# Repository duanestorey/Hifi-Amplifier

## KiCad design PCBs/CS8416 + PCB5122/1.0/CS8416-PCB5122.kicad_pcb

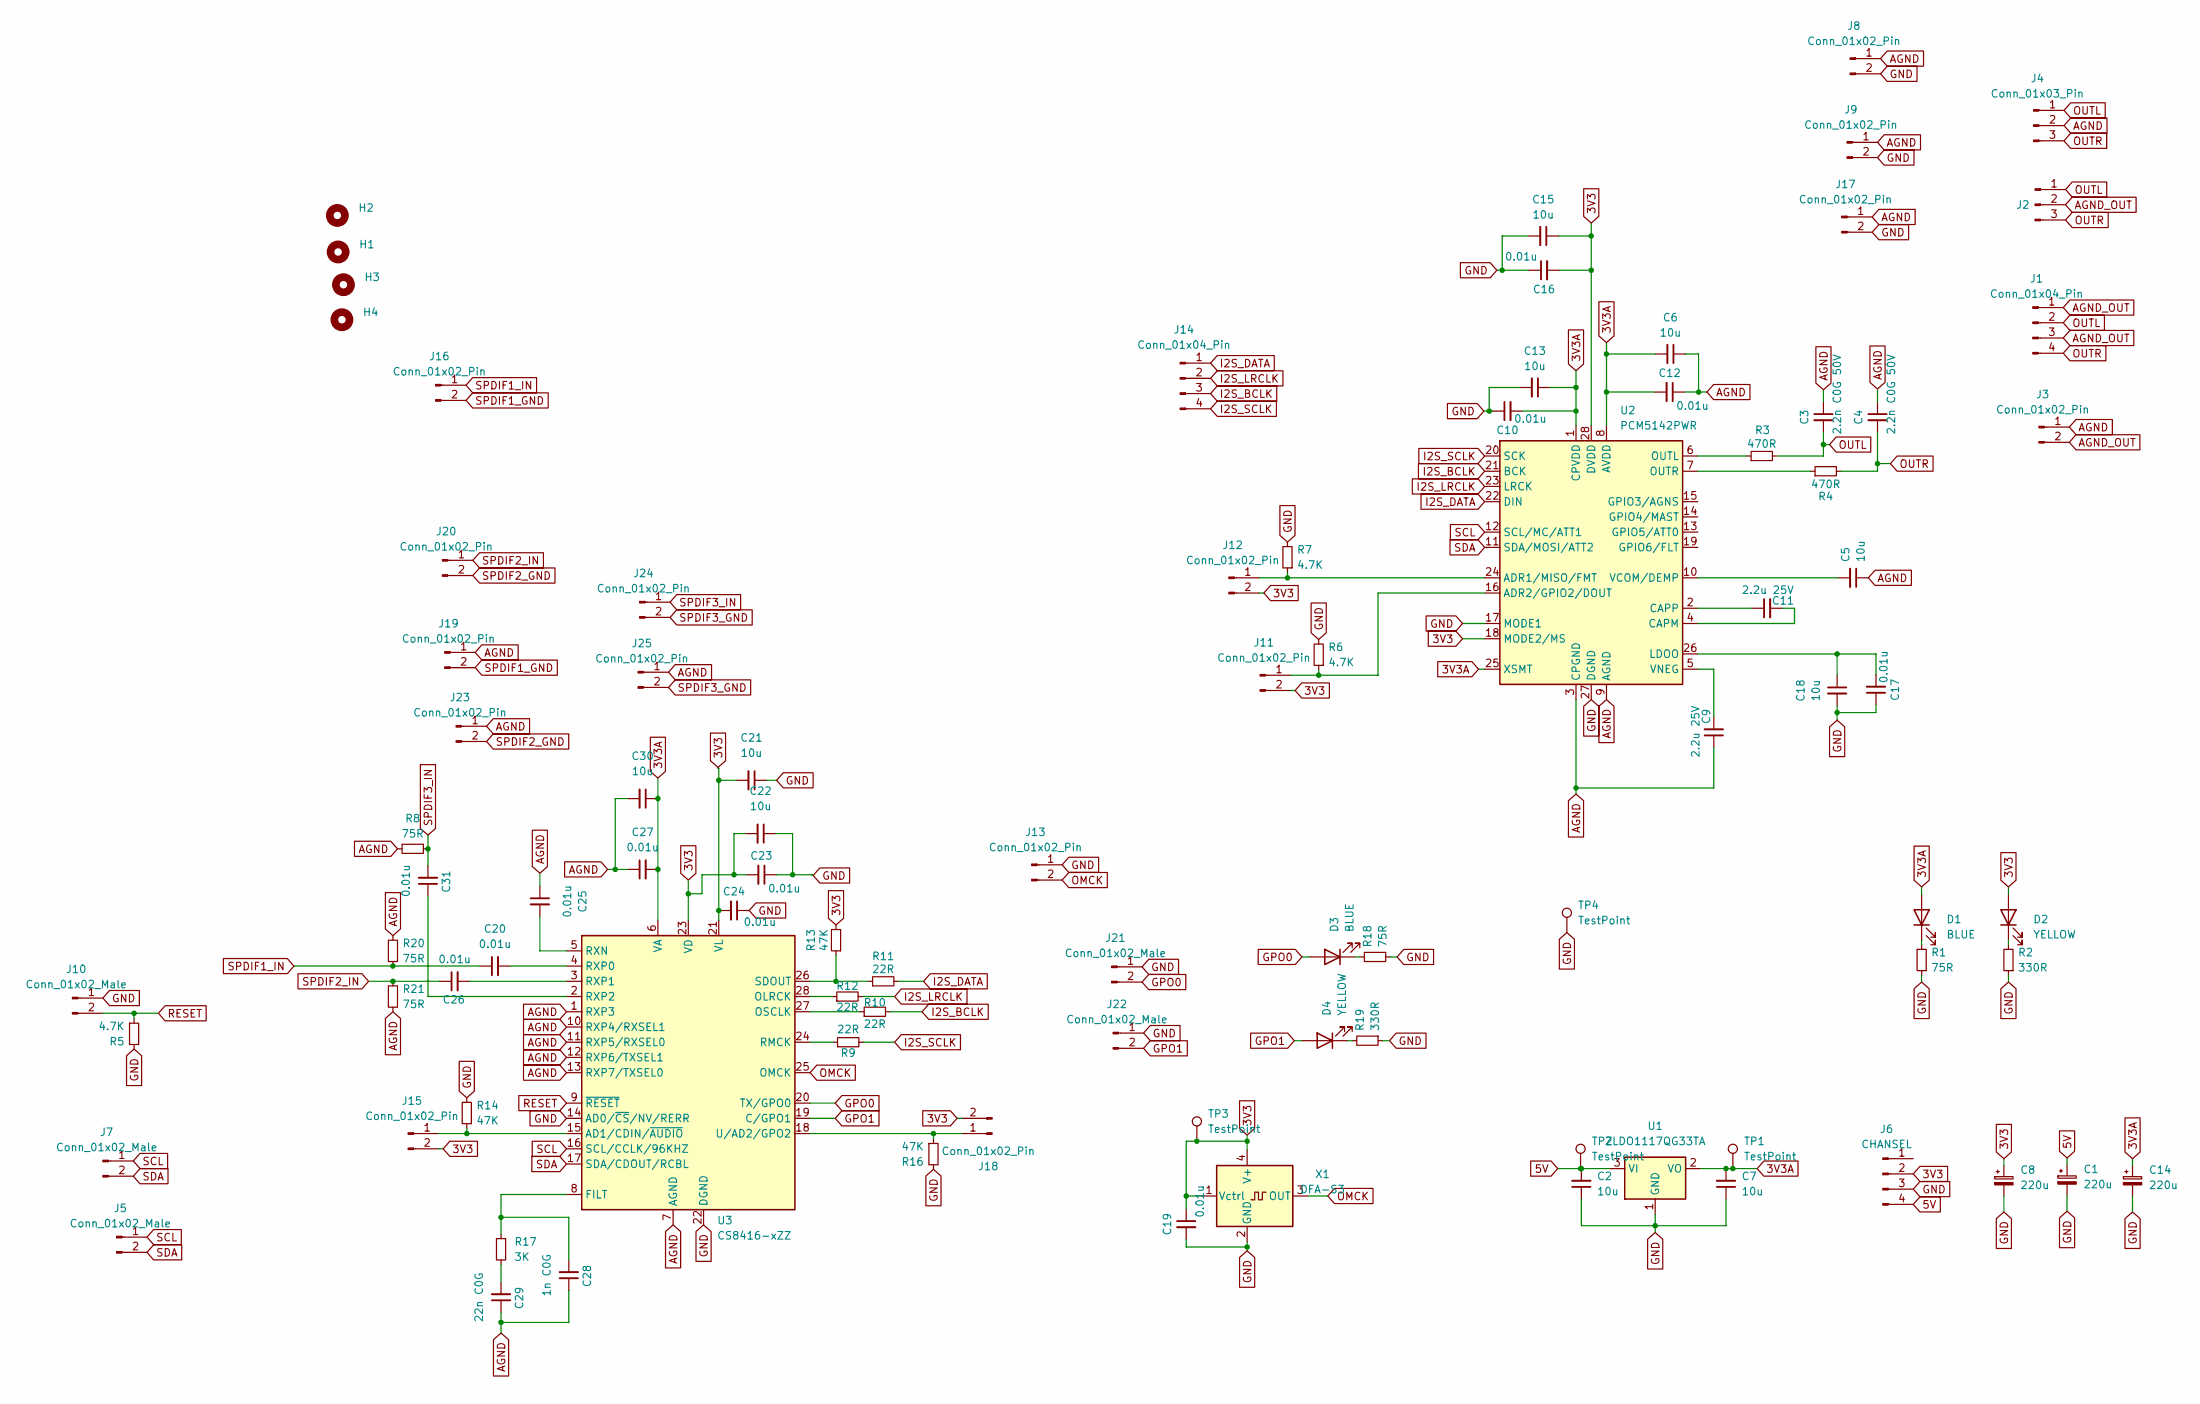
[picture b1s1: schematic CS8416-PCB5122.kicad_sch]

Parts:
C1, C8, C14: 220u; CP_Radial_D6.3mm_P2.50mm
C2, C5, C6, C7, C13, C15, C18, C21, C22, C30: 10u; C_1206_3216Metric_Pad1.33x1.80mm_HandSolder
C3, C4: 2.2n C0G 50V; C_0805_2012Metric
C9, C11: 2.2u 25V; C_0805_2012Metric
C10, C12, C16, C17, C19, C23, C24, C27: 0.01u; C_0805_2012Metric
C20, C25, C26, C31: 0.01u; C_0805_2012Metric_Pad1.18x1.45mm_HandSolder
C28: 1n C0G; C_0805_2012Metric_Pad1.18x1.45mm_HandSolder
C29: 22n C0G; C_0805_2012Metric_Pad1.18x1.45mm_HandSolder
D1, D3: BLUE; LED_0805_2012Metric_Pad1.15x1.40mm_HandSolder
D2, D4: YELLOW; LED_0805_2012Metric_Pad1.15x1.40mm_HandSolder
H1, H2, H3, H4: MountingHole; MountingHole_3.2mm_M3
J1: Conn_01x04_Pin; JST_PH_B4B-PH-K_1x04_P2.00mm_Vertical
J2: Conn_01x03_Pin; JST_PH_B3B-PH-K_1x03_P2.00mm_Vertical
J3, J8, J9, J11, J12, J13, J15, J17, J18, J19, J23, J25: Conn_01x02_Pin; PinHeader_1x02_P2.54mm_Vertical
J4: Conn_01x03_Pin; PinHeader_1x03_P2.54mm_Vertical
J5, J7, J10, J21, J22: Conn_01x02_Male; JST_PH_B2B-PH-K_1x02_P2.00mm_Vertical
J6: CHANSEL; JST_XH_B4B-XH-A_1x04_P2.50mm_Vertical
J14: Conn_01x04_Pin; PinHeader_1x04_P2.54mm_Vertical
J16, J20, J24: Conn_01x02_Pin; JST_XH_B2B-XH-A_1x02_P2.50mm_Vertical
R1, R8, R18, R20, R21: 75R; R_0603_1608Metric_Pad0.98x0.95mm_HandSolder
R2, R19: 330R; R_0603_1608Metric_Pad0.98x0.95mm_HandSolder
R3, R4: 470R; R_0603_1608Metric_Pad0.98x0.95mm_HandSolder
R5, R6, R7: 4.7K; R_0603_1608Metric_Pad0.98x0.95mm_HandSolder
R9, R10, R11, R12: 22R; R_0603_1608Metric_Pad0.98x0.95mm_HandSolder
R13, R14, R16: 47K; R_0603_1608Metric_Pad0.98x0.95mm_HandSolder
R17: 3K; R_0603_1608Metric_Pad0.98x0.95mm_HandSolder
TP1, TP2, TP3, TP4: TestPoint; TestPoint_Pad_2.0x2.0mm
U1: ZLDO1117QG33TA; SOT-223-3_TabPin2
U2: PCM5142PWR; TSSOP-28_4.4x9.7mm_P0.65mm
U3: CS8416-xZZ; TSSOP-28_4.4x9.7mm_P0.65mm
X1: DFA-S3; Oscillator_SMD_EuroQuartz_XO53-4Pin_5.0x3.2mm

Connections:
3V3: C8.1, C15.1, C16.2, C19.1, C21.2, C22.2, C23.2, C24.2, D2.2 (A), J6.2, J11.2, J12.2, J15.2, J18.2, R13.2, TP3.1, U2.18 (MODE2/MS), U2.28 (DVDD), U3.21 (VL), U3.23 (VD), X1.1 (Vctrl), X1.4 (V+)
3V3A: C6.2, C7.2, C10.2, C12.2, C13.1, C14.1, C27.2, C30.1, D1.2 (A), TP1.1, U1.2 (VO), U2.1 (CPVDD), U2.8 (AVDD), U2.25 (XSMT), U3.6 (VA)
5V: C1.1, C2.2, J6.4, TP2.1, U1.3 (VI)
AGND: C3.1, C4.1, C5.1, C6.1, C9.1, C12.1, C25.1, C27.1, C28.1, C29.1, C30.2, J3.1, J4.2, J8.1, J9.1, J17.1, J19.1, J23.1, J25.1, R8.2, R20.2, R21.1, U2.3 (CPGND), U2.9 (AGND), U3.1 (RXP3), U3.7 (AGND), U3.10 (RXP4/RXSEL1), U3.11 (RXP5/RXSEL0), U3.12 (RXP6/TXSEL1), U3.13 (RXP7/TXSEL0)
AGND_OUT: J1.1, J1.3, J2.2, J3.2
GND: C1.2, C2.1, C7.1, C8.2, C10.1, C13.2, C14.2, C15.2, C16.1, C17.1, C18.2, C19.2, C21.1, C22.1, C23.1, C24.1, J6.3, J8.2, J9.2, J10.1, J13.1, J17.2, J21.1, J22.1, R1.1, R2.1, R5.2, R6.2, R7.2, R14.2, R16.2, R18.1, R19.1, TP4.1, U1.1 (GND), U2.17 (MODE1), U2.27 (DGND), U3.14 (AD0/~CS/NV/RERR), U3.22 (DGND), X1.2 (GND)
GPO0: D3.2 (A), J21.2, U3.20 (TX/GPO0)
GPO1: D4.2 (A), J22.2, U3.19 (C/GPO1)
I2S_BCLK: J14.3, R10.2, U2.21 (BCK)
I2S_DATA: J14.1, R11.2, U2.22 (DIN)
I2S_LRCLK: J14.2, R12.2, U2.23 (LRCK)
I2S_SCLK: J14.4, R9.2, U2.20 (SCK)
unnamed: C29.2, R17.2
unnamed: D1.1 (K), R1.2
unnamed: D2.1 (K), R2.2
unnamed: D3.1 (K), R18.2
unnamed: D4.1 (K), R19.2
unnamed: J11.1, R6.1, U2.16 (ADR2/GPIO2/DOUT)
unnamed: J12.1, R7.1, U2.24 (ADR1/MISO/FMT)
unnamed: J15.1, R14.1, U3.15 (AD1/CDIN/~AUDIO)
unnamed: J18.1, R16.1, U3.18 (U/AD2/GPO2)
unnamed: C11.2, U2.4 (CAPM)
unnamed: C11.1, U2.2 (CAPP)
unnamed: C17.2, C18.1, U2.26 (LDOO)
unnamed: R3.1, U2.6 (OUTL)
unnamed: R4.1, U2.7 (OUTR)
unnamed: C5.2, U2.10 (VCOM/DEMP)
unnamed: C9.2, U2.5 (VNEG)
unnamed: C28.2, R17.1, U3.8 (FILT)
unnamed: R12.1, U3.28 (OLRCK)
unnamed: R10.1, U3.27 (OSCLK)
unnamed: R9.1, U3.24 (RMCK)
unnamed: C25.2, U3.5 (RXN)
unnamed: C20.2, U3.4 (RXP0)
unnamed: C26.2, U3.3 (RXP1)
unnamed: C31.1, U3.2 (RXP2)
unnamed: R11.1, R13.1, U3.26 (SDOUT)
OMCK: J13.2, U3.25 (OMCK), X1.3 (OUT)
OUTL: C3.2, J1.2, J2.1, J4.1, R3.2
OUTR: C4.2, J1.4, J2.3, J4.3, R4.2
RESET: J10.2, R5.1, U3.9 (~RESET)
SCL: J5.1, J7.1, U2.12 (SCL/MC/ATT1), U3.16 (SCL/CCLK/96KHZ)
SDA: J5.2, J7.2, U2.11 (SDA/MOSI/ATT2), U3.17 (SDA/CDOUT/RCBL)
SPDIF1_GND: J16.2, J19.2
SPDIF1_IN: C20.1, J16.1, R20.1
SPDIF2_GND: J20.2, J23.2
SPDIF2_IN: C26.1, J20.1, R21.2
SPDIF3_GND: J24.2, J25.2
SPDIF3_IN: C31.2, J24.1, R8.1

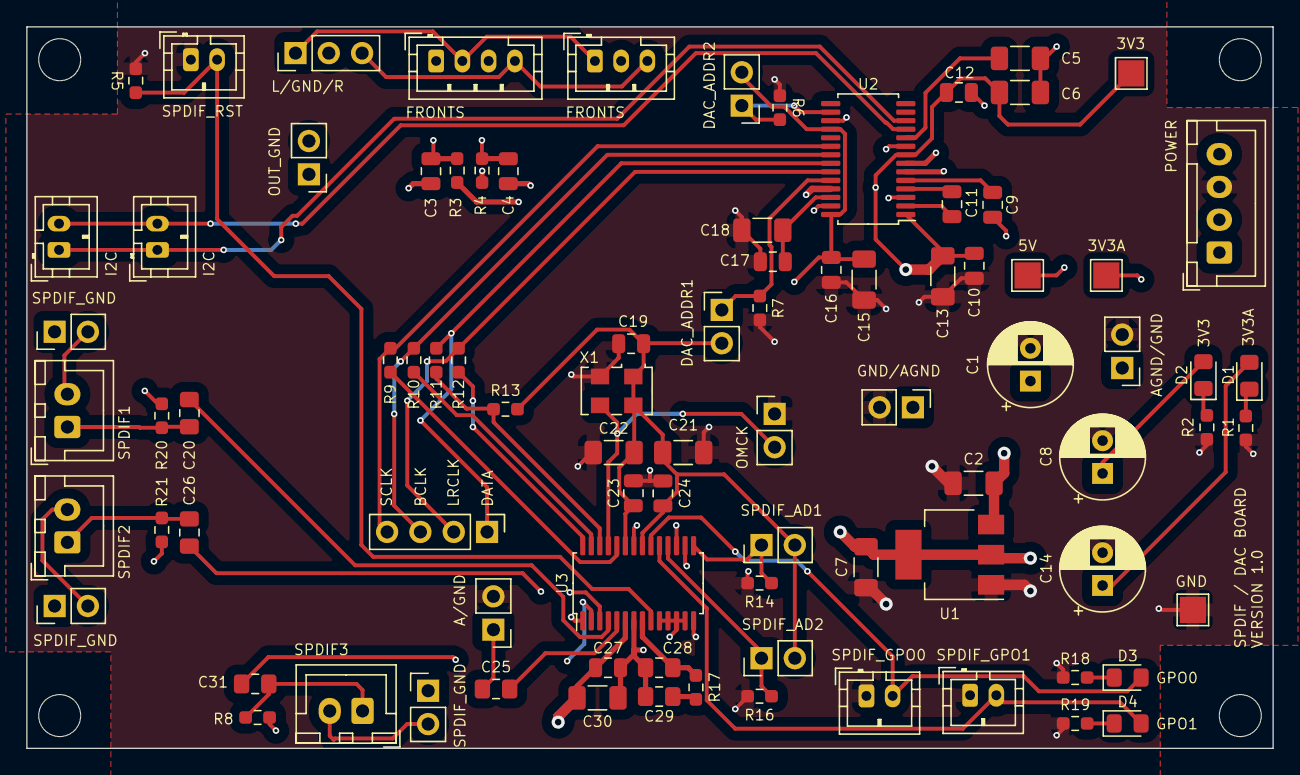
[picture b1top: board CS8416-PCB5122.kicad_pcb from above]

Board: 4 copper layers, 95.0 x 55.0 mm, 92 parts (0 on the bottom side), 49 nets.

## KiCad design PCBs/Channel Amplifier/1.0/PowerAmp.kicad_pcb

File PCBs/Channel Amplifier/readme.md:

# LM3886 Channel Amplifiers

The LM3886 has a somewhat mythical status ever since a $3,000 gaincard was released in 1999.  It had amazing sound quality, but inside was only a tweaked LM3886 Texas Instrument 68W amplifier IC.  Since then, an entire community has evolved around these 'gainclones', which truly are hi-fidelity.  This project uses 5 of these, along with a Dolby Decoder IC, to create a complete DIY hi-fidelity 5.1 system.

## Version History

- 1.0: Initial Release
- 1.1: Improved layout
- 1.2: Changed erroneous capacitor size

## Speciality Components

* LM3886 68W channel amplifier ICs
* 680pF, and 47pF silver mica capacitors
* 4.7uF X7R 50V caps
* 10uf Nichicon Muse ES

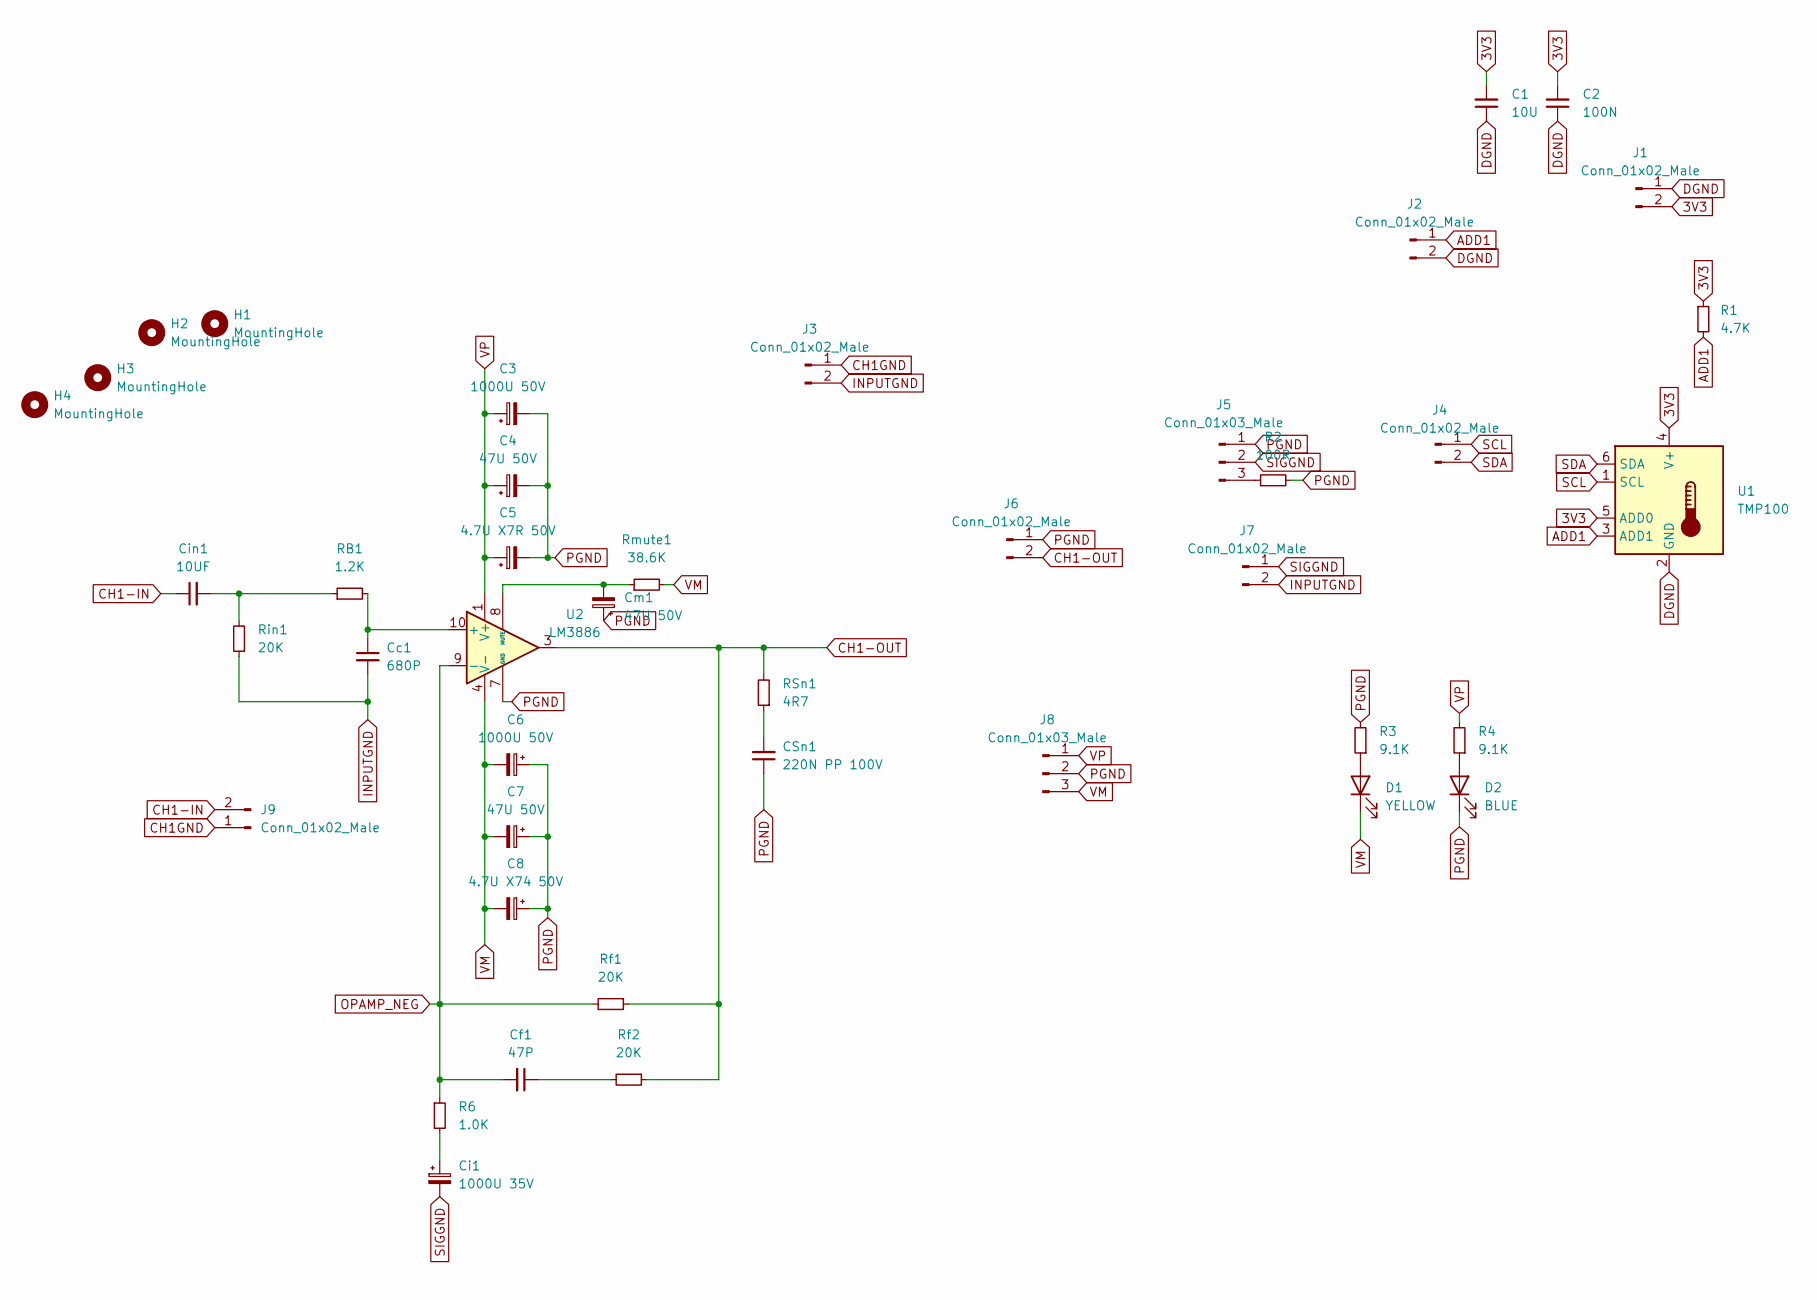
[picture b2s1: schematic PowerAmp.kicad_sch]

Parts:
C1: 10U; R_1206_3216Metric_Pad1.30x1.75mm_HandSolder
C2: 100N; R_0805_2012Metric_Pad1.20x1.40mm_HandSolder
C3, C6: 1000U 50V; CP_Radial_D12.5mm_P5.00mm
C4, C7: 47U 50V; CP_Radial_D6.3mm_P2.50mm
C5: 4.7U X7R 50V; C_Disc_D6.0mm_W4.4mm_P5.00mm
C8: 4.7U X74 50V; C_Disc_D6.0mm_W4.4mm_P5.00mm
CSn1: 220N PP 100V; C_Rect_L18.0mm_W7.0mm_P15.00mm_FKS3_FKP3
Cc1: 680P; C_Disc_D11.0mm_W5.0mm_P10.00mm
Cf1: 47P; C_Disc_D9.0mm_W5.0mm_P7.50mm
Ci1: 1000U 35V; CP_Radial_D16.0mm_P7.50mm
Cin1: 10UF; CP_Radial_D5.0mm_P2.00mm
Cm1: 47U 50V; CP_Radial_D6.3mm_P2.50mm
D1: YELLOW; LED_0805_2012Metric_Pad1.15x1.40mm_HandSolder
D2: BLUE; LED_0805_2012Metric_Pad1.15x1.40mm_HandSolder
H1, H2, H3, H4: MountingHole; MountingHole_3mm
J1, J4, J9: Conn_01x02_Male; JST_PH_B2B-PH-K_1x02_P2.00mm_Vertical
J2, J3, J7: Conn_01x02_Male; PinHeader_1x02_P2.54mm_Vertical
J5: Conn_01x03_Male; PinHeader_1x03_P2.54mm_Vertical
J6: Conn_01x02_Male; JST_VH_B2P-VH_1x02_P3.96mm_Vertical
J8: Conn_01x03_Male; JST_VH_B3P-VH-B_1x03_P3.96mm_Vertical
R1: 4.7K; R_0603_1608Metric_Pad0.98x0.95mm_HandSolder
R2: 100R; R_0805_2012Metric_Pad1.20x1.40mm_HandSolder
R3, R4: 9.1K; R_0805_2012Metric_Pad1.20x1.40mm_HandSolder
R6: 1.0K; R_Axial_DIN0207_L6.3mm_D2.5mm_P10.16mm_Horizontal
RB1: 1.2K; R_Axial_DIN0207_L6.3mm_D2.5mm_P10.16mm_Horizontal
RSn1: 4R7; R_Axial_DIN0411_L9.9mm_D3.6mm_P12.70mm_Horizontal
Rf1, Rf2: 20K; R_Axial_DIN0207_L6.3mm_D2.5mm_P10.16mm_Horizontal
Rin1: 20K; R_Axial_DIN0207_L6.3mm_D2.5mm_P10.16mm_Horizontal
Rmute1: 38.6K; R_Axial_DIN0207_L6.3mm_D2.5mm_P10.16mm_Horizontal
U1: TMP100; SOT-23-6
U2: LM3886; TO-220-11_P3.4x5.08mm_StaggerOdd_Lead4.85mm_Vertical

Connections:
3V3: C1.2, C2.2, J1.2, R1.1, U1.4 (V+), U1.5 (ADD0)
ADD1: J2.1, R1.2, U1.3 (ADD1)
CH1-IN: Cin1.1, J9.2
CH1-OUT: J6.2, RSn1.2, Rf1.1, Rf2.1, U2.3
CH1GND: J3.1, J9.1
DGND: C1.1, C2.1, J1.1, J2.2, U1.2 (GND)
INPUTGND: Cc1.2, J3.2, J7.2, Rin1.1
unnamed: CSn1.2, RSn1.1
unnamed: Cf1.1, Rf2.2
unnamed: Ci1.1, R6.2
unnamed: Cin1.2, RB1.1, Rin1.2
unnamed: D1.2 (A), R3.1
unnamed: D2.2 (A), R4.1
unnamed: J5.3, R2.1
unnamed: Cc1.1, RB1.2, U2.10 (+)
unnamed: Cm1.2, Rmute1.1, U2.8 (MUTE)
OPAMP_NEG: Cf1.2, R6.1, Rf1.2, U2.9 (-)
PGND: C3.2, C4.2, C5.2, C6.1, C7.1, C8.1, CSn1.1, Cm1.1, D2.1 (K), J5.1, J6.1, J8.2, R2.2, R3.2, U2.7 (GND)
SCL: J4.1, U1.1 (SCL)
SDA: J4.2, U1.6 (SDA)
SIGGND: Ci1.2, J5.2, J7.1
VM: C6.2, C7.2, C8.2, D1.1 (K), J8.3, Rmute1.2, U2.4 (V-)
VP: C3.1, C4.1, C5.1, J8.1, R4.2, U2.1 (V+), U2.5 (V+)

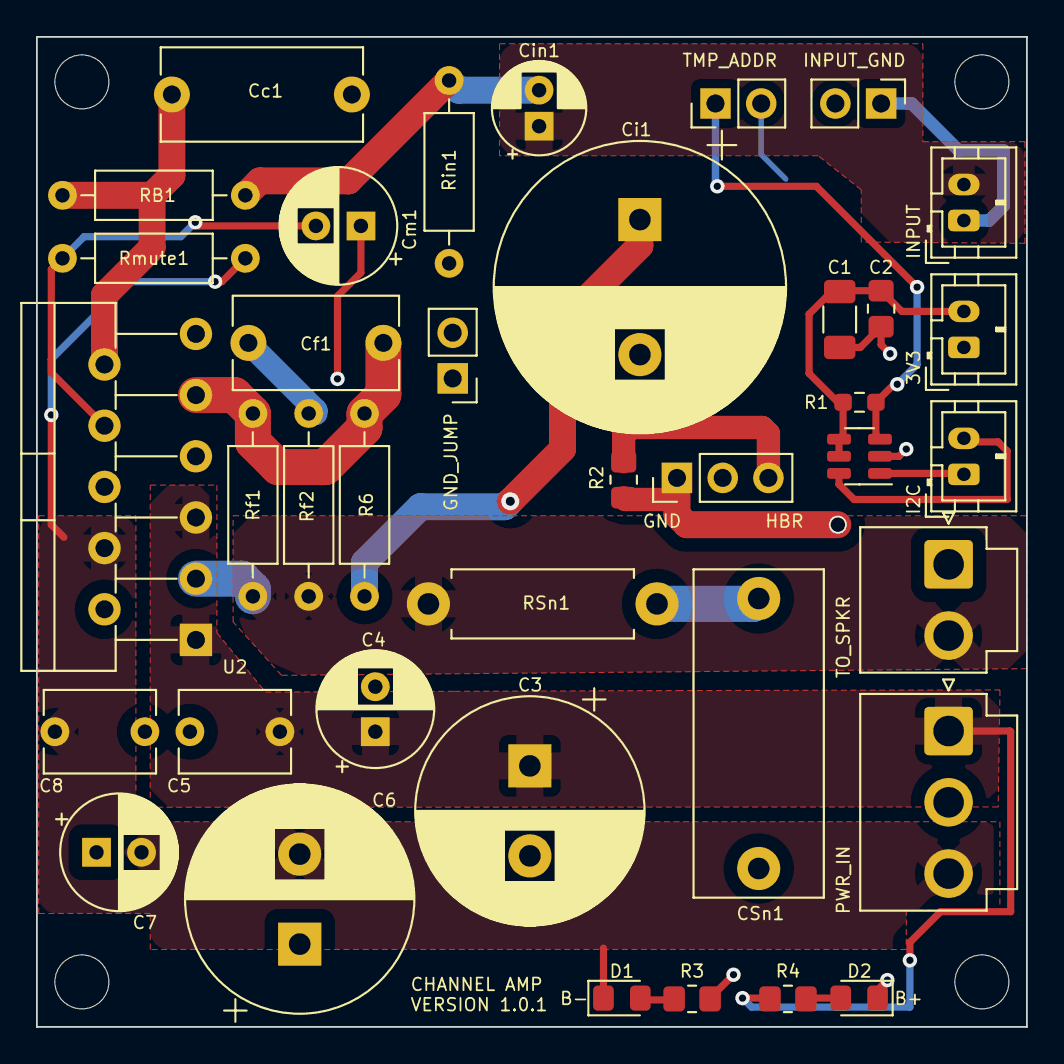
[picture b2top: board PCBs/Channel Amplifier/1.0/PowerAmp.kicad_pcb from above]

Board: 2 copper layers, 55.0 x 55.0 mm, 42 parts (0 on the bottom side), 23 nets.

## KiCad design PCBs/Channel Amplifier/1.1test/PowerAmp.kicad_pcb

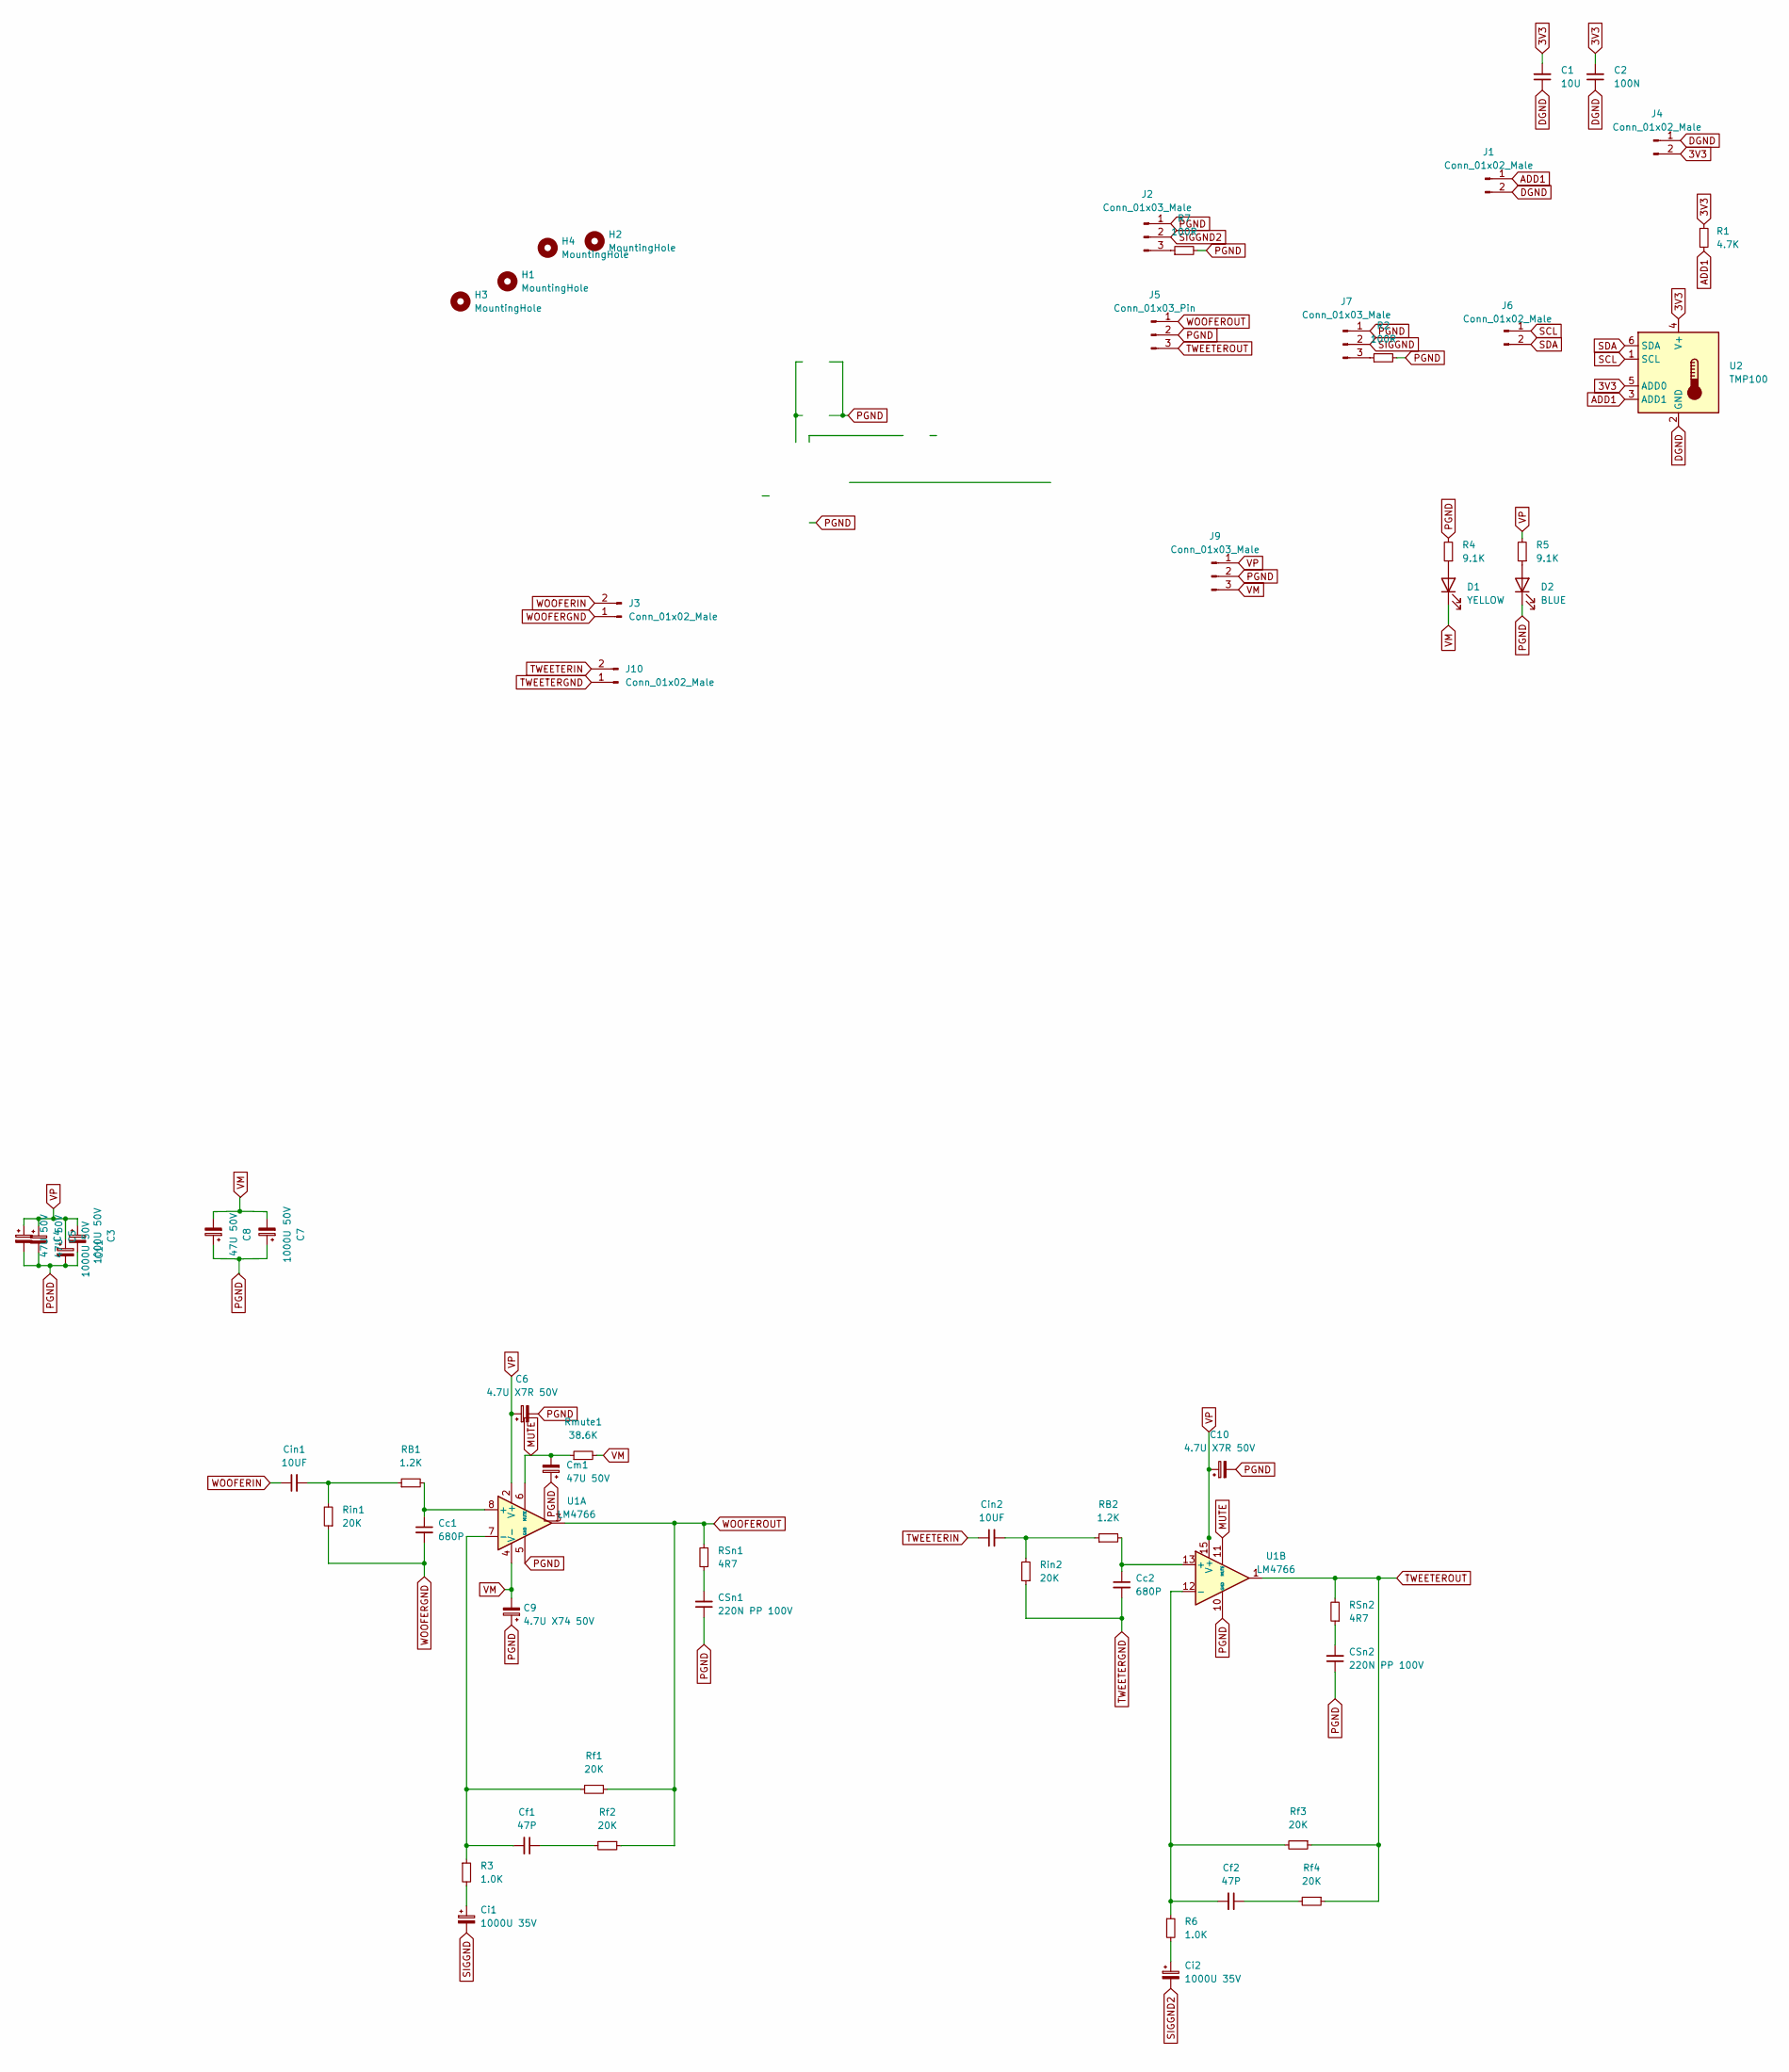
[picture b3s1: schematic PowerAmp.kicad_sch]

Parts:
C1: 10U; R_1206_3216Metric_Pad1.30x1.75mm_HandSolder
C2: 100N; R_0805_2012Metric_Pad1.20x1.40mm_HandSolder
C3, C7, C11: 1000U 50V; CP_Radial_D12.5mm_P5.00mm
C4, C5, C8: 47U 50V; CP_Radial_D6.3mm_P2.50mm
C6, C10: 4.7U X7R 50V; C_Disc_D6.0mm_W4.4mm_P5.00mm
C9: 4.7U X74 50V; C_Disc_D6.0mm_W4.4mm_P5.00mm
CSn1, CSn2: 220N PP 100V; C_Rect_L18.0mm_W7.0mm_P15.00mm_FKS3_FKP3
Cc1, Cc2: 680P; C_1206_3216Metric_Pad1.33x1.80mm_HandSolder
Cf1, Cf2: 47P; C_1206_3216Metric_Pad1.33x1.80mm_HandSolder
Ci1, Ci2: 1000U 35V; CP_Radial_D12.5mm_P5.00mm
Cin1, Cin2: 10UF; CP_Radial_D5.0mm_P2.00mm
Cm1: 47U 50V; CP_Radial_D6.3mm_P2.50mm
D1: YELLOW; LED_0805_2012Metric_Pad1.15x1.40mm_HandSolder
D2: BLUE; LED_0805_2012Metric_Pad1.15x1.40mm_HandSolder
H1, H2, H3, H4: MountingHole; MountingHole_3mm
J1: Conn_01x02_Male; PinHeader_1x02_P2.54mm_Vertical
J2, J7: Conn_01x03_Male; PinHeader_1x03_P2.54mm_Vertical
J3, J4, J6, J10: Conn_01x02_Male; JST_PH_B2B-PH-K_1x02_P2.00mm_Vertical
J5: Conn_01x03_Pin; JST_VH_B3P-VH_1x03_P3.96mm_Vertical
J9: Conn_01x03_Male; JST_VH_B3P-VH-B_1x03_P3.96mm_Vertical
R1: 4.7K; R_0603_1608Metric_Pad0.98x0.95mm_HandSolder
R2, R7: 100R; R_0805_2012Metric_Pad1.20x1.40mm_HandSolder
R3, R6: 1.0K; R_1206_3216Metric_Pad1.30x1.75mm_HandSolder
R4, R5: 9.1K; R_0805_2012Metric_Pad1.20x1.40mm_HandSolder
RB1, RB2: 1.2K; R_1206_3216Metric_Pad1.30x1.75mm_HandSolder
RSn1, RSn2: 4R7; R_Axial_DIN0411_L9.9mm_D3.6mm_P12.70mm_Horizontal
Rf1, Rf2, Rf3, Rf4: 20K; R_1206_3216Metric_Pad1.30x1.75mm_HandSolder
Rin1, Rin2: 20K; R_1206_3216Metric_Pad1.30x1.75mm_HandSolder
Rmute1: 38.6K; R_1206_3216Metric_Pad1.30x1.75mm_HandSolder
U1: LM4766; TO-220-15_P2.54x2.54mm_StaggerOdd_Lead4.58mm_Vertical
U2: TMP100; SOT-23-6

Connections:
3V3: C1.2, C2.2, J4.2, R1.1, U2.4 (V+), U2.5 (ADD0)
ADD1: J1.1, R1.2, U2.3 (ADD1)
DGND: C1.1, C2.1, J1.2, J4.1, U2.2 (GND)
MUTE: Cm1.2, Rmute1.1, U1.6 (MUTE), U1.11 (MUTE)
unnamed: CSn1.2, RSn1.1
unnamed: CSn2.2, RSn2.1
unnamed: Cf1.1, Rf2.2
unnamed: Cf2.1, Rf4.2
unnamed: Ci1.1, R3.2
unnamed: Ci2.1, R6.2
unnamed: Cin1.2, RB1.1, Rin1.2
unnamed: Cin2.2, RB2.1, Rin2.2
unnamed: D1.2 (A), R4.1
unnamed: D2.2 (A), R5.1
unnamed: J2.3, R7.1
unnamed: J7.3, R2.1
unnamed: Cc1.1, RB1.2, U1.8 (+)
unnamed: Cf1.2, R3.1, Rf1.2, U1.7 (-)
unnamed: Cc2.1, RB2.2, U1.13 (+)
unnamed: Cf2.2, R6.1, Rf3.2, U1.12 (-)
PGND: C3.2, C4.2, C5.2, C6.2, C7.1, C8.1, C9.1, C10.2, C11.2, CSn1.1, CSn2.1, Cm1.1, D2.1 (K), J2.1, J5.2, J7.1, J9.2, R2.2, R4.2, R7.2, U1.5 (GND), U1.10 (GND)
SCL: J6.1, U2.1 (SCL)
SDA: J6.2, U2.6 (SDA)
SIGGND: Ci1.2, J7.2
SIGGND2: Ci2.2, J2.2
TWEETERGND: Cc2.2, J10.1, Rin2.1
TWEETERIN: Cin2.1, J10.2
TWEETEROUT: J5.3, RSn2.2, Rf3.1, Rf4.1, U1.1
VM: C7.2, C8.2, C9.2, D1.1 (K), J9.3, Rmute1.2, U1.4 (V-)
VP: C3.1, C4.1, C5.1, C6.1, C10.1, C11.1, J9.1, R5.2, U1.2 (V+), U1.15 (V+)
WOOFERGND: Cc1.2, J3.1, Rin1.1
WOOFERIN: Cin1.1, J3.2
WOOFEROUT: J5.1, RSn1.2, Rf1.1, Rf2.1, U1.3

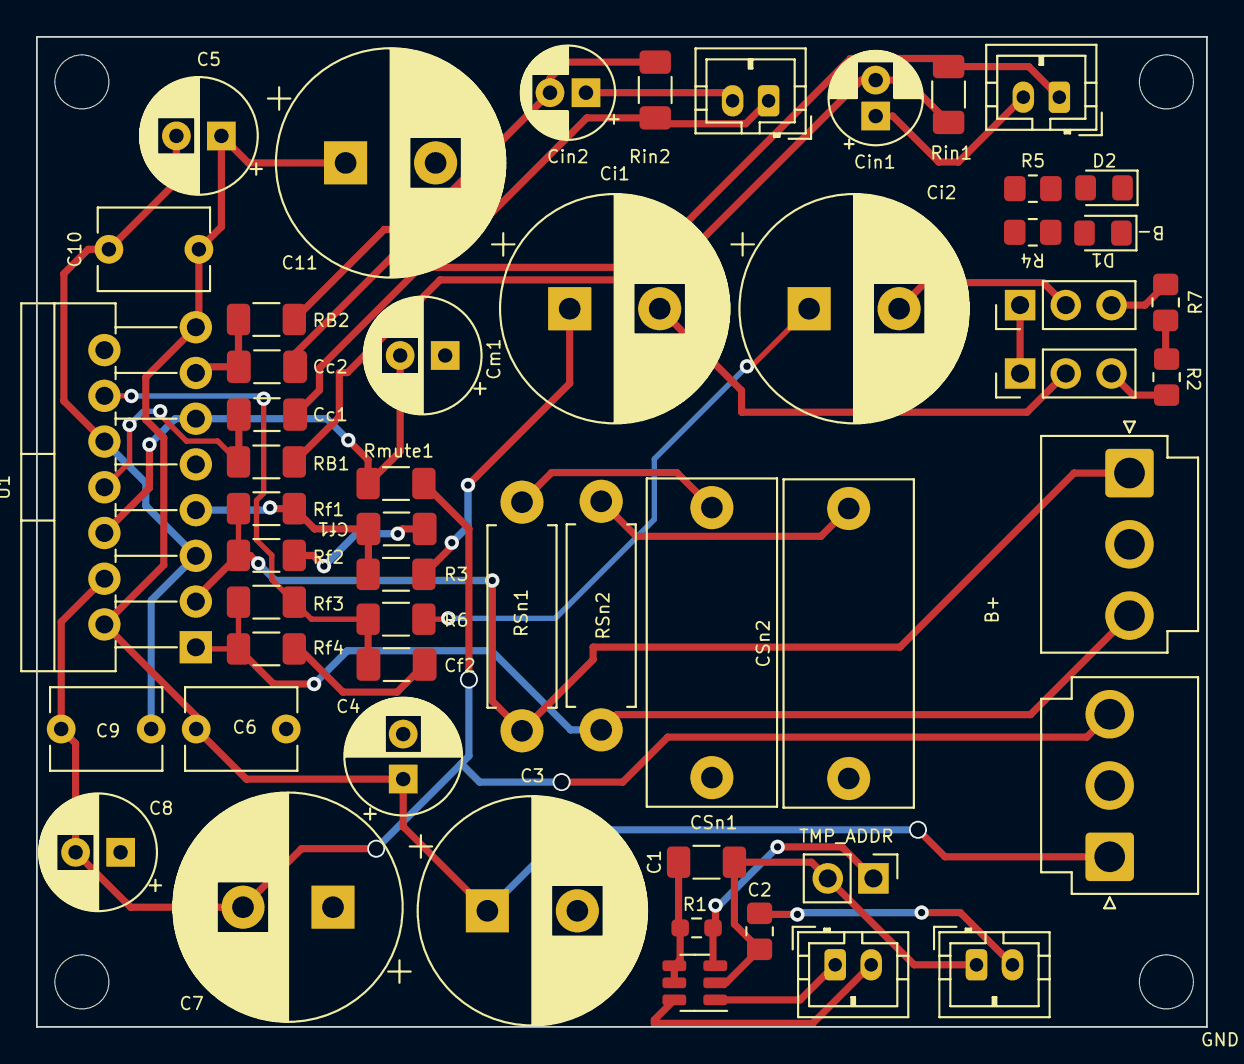
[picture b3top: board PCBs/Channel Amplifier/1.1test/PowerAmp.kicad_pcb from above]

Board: 2 copper layers, 65.0 x 55.0 mm, 57 parts (0 on the bottom side), 33 nets.
